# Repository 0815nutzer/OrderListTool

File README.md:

# OrderListTool
Create an order list from a BOM

Documentation: https://github.com/0815nutzer/OrderListTool/wiki

Dependencies: python3-pyqt5

English description see below.

## German description
Mit Hilfe dieses kleinen Werkzeugs soll eine automatisierte Zuordnung von Bestellnummern zu Bauteilen in einem Schaltplan erfolgen.
Die Bauteile des Schaltplan müssen hierfür in einer entsprechend formatierten csv-Datei zur Verfügung stehen, während die "Bauteildatenbank", welche die zuzuordnenden Bestellnummern enthält, aus entsprechend formatierten Textdateien besteht.

Eine ausführlichere Dokumentation befindet sich im Wiki dieses Projekts: https://github.com/0815nutzer/OrderListTool/wiki

### Anwendung
1. Erzeugen einer Stückliste im csv-Format unter Verwendung des dem CAD-System entsprechenden Skripts im Ordner "BOM-Scripts"
2. Das Programm durch Ausführen der `main.py` mit Python3 starten
3. Mit Klick auf "Stückliste" die zuvor erstellte Stückliste im csv-Fomat wählen
4. Durch Klick auf "Bestelllisten" den Ordner mit den Bestelllisten wählen
5. Paare durch klicken auf "Suche Paare" suchen lassen
6. Die gefundenen Paare prüfen und wenn nötig, Änderungen in der Auswahl vornehmen
7. Mit Klick auf "exp. Bestellliste" die lieferantenspezifischen Bestelllisten generieren lassen

## English description

### Usage
1. Open schematic and create a BOM-file in csv-format using the appropriate script in the "BOM-Scripts"-folder
2. Start the tool by running `main.py` using python3
3. Select the prior created csv-file
4. Select the path to the folder containing the partlist-files
5. Click `Search pairs`
6. Review found matches and adjust, if required
7. Click `Export lists` to create distribtor dependend order lists

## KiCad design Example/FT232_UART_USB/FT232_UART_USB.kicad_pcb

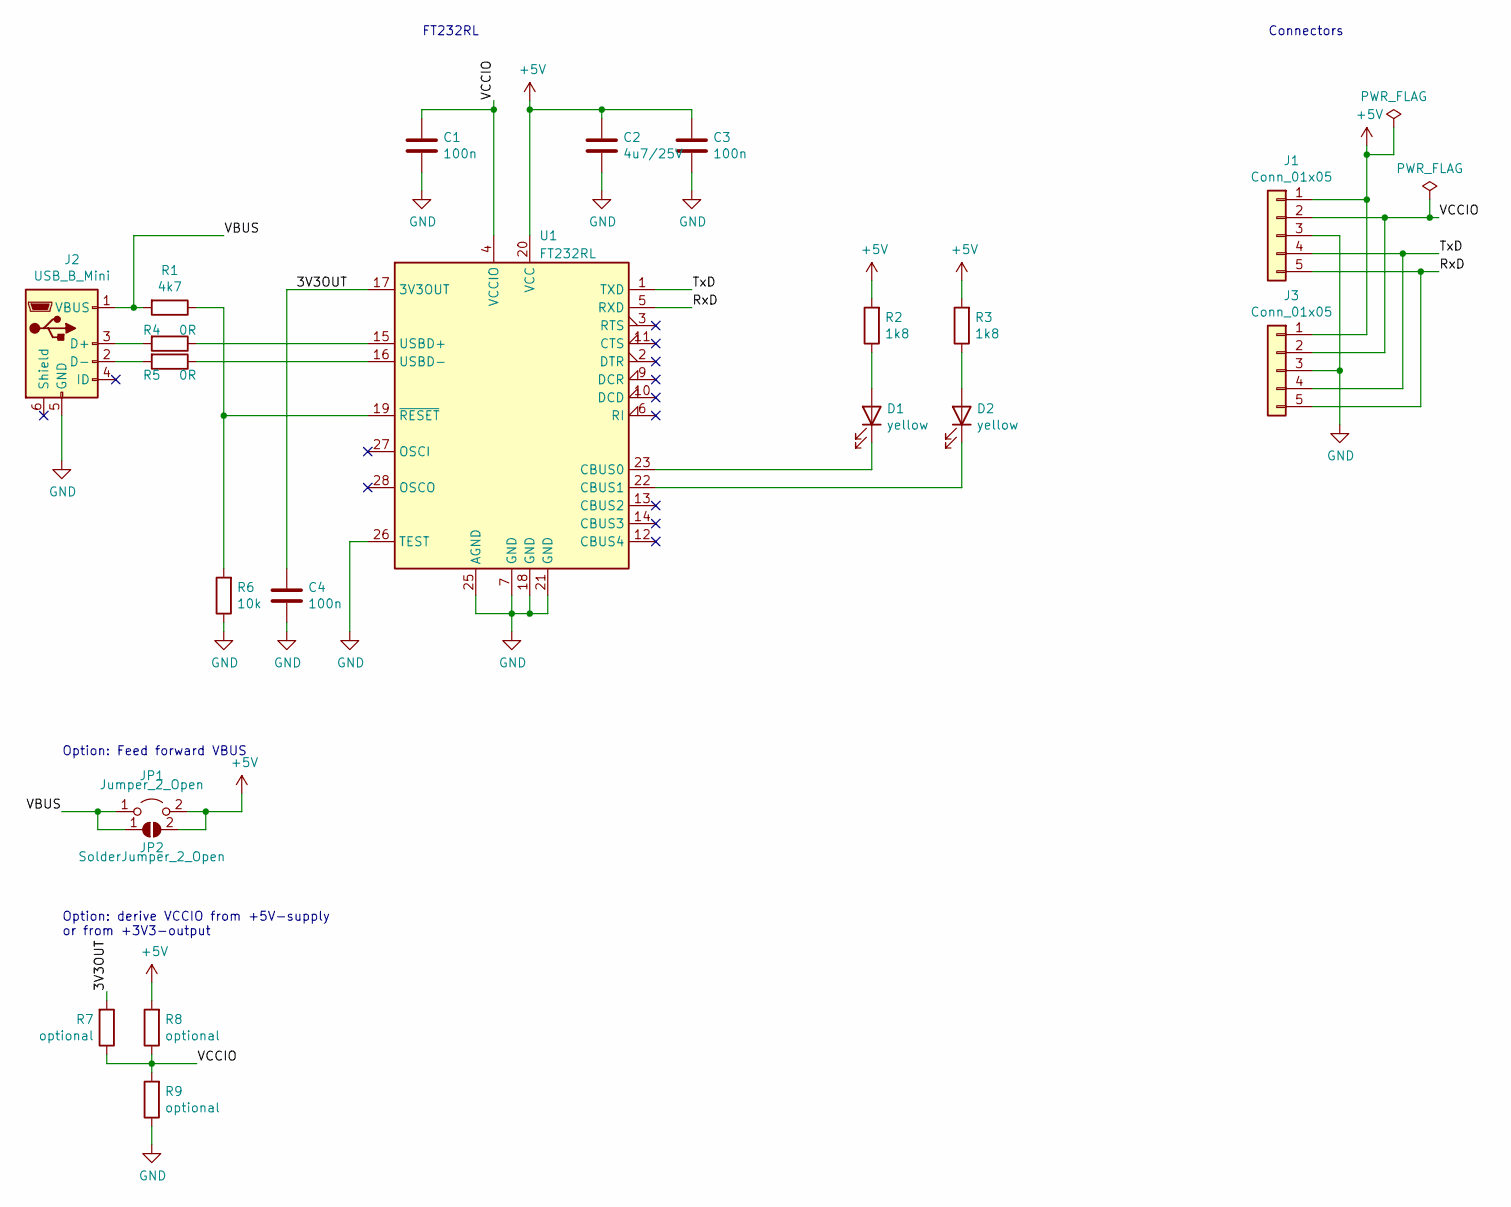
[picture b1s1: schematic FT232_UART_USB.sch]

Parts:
C1, C3, C4: 100n; C_0603_1608Metric
C2: 4u7/25V; C_1206_3216Metric
D1, D2: yellow; LED_0603_1608Metric
J1, J3: Conn_01x05; PinHeader_1x05_P2.54mm_Vertical
J2: USB_B_Mini; USB_Mini-B_Wuerth_65100516121_Horizontal
JP1: Jumper_2_Open; PinHeader_1x02_P2.54mm_Vertical
JP2: SolderJumper_2_Open; SolderJumper-2_P1.3mm_Open_TrianglePad1.0x1.5mm
R1: 4k7; R_0603_1608Metric
R2, R3: 1k8; R_0603_1608Metric
R4, R5: 0R; R_0603_1608Metric
R6: 10k; R_0603_1608Metric
R7, R8, R9: optional; R_0603_1608Metric
U1: FT232RL; SSOP-28_5.3x10.2mm_P0.65mm

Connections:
+5V: C2.1, C3.1, J1.1, J3.1, JP1.2 (B), JP2.2 (B), R2.2, R3.2, R8.2, U1.20 (VCC)
/3V3OUT: C4.1, R7.2, U1.17 (3V3OUT)
/RxD: J1.5, J3.5, U1.5 (RXD)
/TxD: J1.4, J3.4, U1.1 (TXD)
/VBUS: J2.1 (VBUS), JP1.1 (A), JP2.1 (A), R1.2
/VCCIO: C1.1, J1.2, J3.2, R7.1, R8.1, R9.2, U1.4 (VCCIO)
GND: C1.2, C2.2, C3.2, C4.2, J1.3, J2.5 (GND), J3.3, R6.1, R9.1, U1.7 (GND), U1.18 (GND), U1.21 (GND), U1.25 (AGND), U1.26 (TEST)
unnamed: D1.1 (K), U1.23 (CBUS0)
unnamed: D1.2 (A), R2.1
unnamed: D2.1 (K), U1.22 (CBUS1)
unnamed: D2.2 (A), R3.1
unnamed: J2.2 (D-), R5.2
unnamed: J2.3 (D+), R4.2
unnamed: R1.1, R6.2, U1.19 (~RESET~)
unnamed: R4.1, U1.15 (USBD+)
unnamed: R5.1, U1.16 (USBD-)

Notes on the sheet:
FT232RL
Connectors
Option: Feed forward VBUS
Option: derive VCCIO from +5V-supply or from +3V3-output

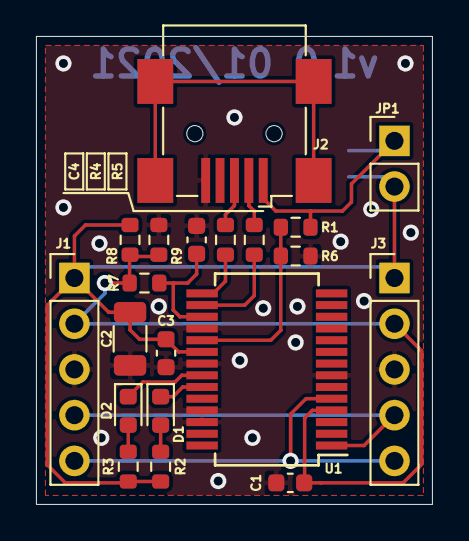
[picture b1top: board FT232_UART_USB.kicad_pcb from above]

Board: 2 copper layers, 22.0 x 26.0 mm, 21 parts (1 on the bottom side), 16 nets.

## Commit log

2021-03-25 initialer Stand des Programms hinzugefügt, Weiterentwicklung des Programms nun als eigenständiges Git-Projekt
2021-03-25 Dokumentation durch Anpassung der Readme-Datei begonnen.
2021-03-26 Mehrsprachigkeit implementiert. language.py beinhaltet die Texte der jeweiligen Sprache (aktuell Deutsch und Englisch) und kann beliebig für jede Sprache erweitert werden. Auswahl der Sprach erfolgt 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
2021-03-26 fehlende Sprachdatei nachgeliefert, kleiner Anpassung bezüglich der Definitionen
2021-03-30 Für Bestelllisten zu ignorierende Bauteile werden bei der Gesamtübersicht nicht mehr ignoriert, diverse Anpassungen im Zusammenhang mit der Dokumentation
2021-03-30 Lizenzinformationen hinzugefügt (GPLv3)
2021-03-30 Lizenz auf oberste Ebene verschoben
2021-04-03 Den USB_UART_Adapter als KiCAD-Projekt in Beispiele eingefügt, um auch die BOM-Skripte erproben zu können
2021-04-03 Verweis auf Wiki zu README hinzugefügt.
2021-04-19 Stücklisten um Eigenschaft "Herstellerbezeichnung" (Manufacturer -> MANNUM) erweitert, damit Bestücklisten für Hersteller erzeugt werden können, da diese die Herstellernummer anstelle der Bestellnumm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
2021-04-19 Eigenschaft "manNum" (Herstellerbezeichnung) hinzugefügt, um Bestückungslisten für Platinenfertiger zu generieren
2021-06-30 Symbol K (Relais) zu Teiletyp "mechanics" hinzugefügt
2021-08-13 Abhängigkeit von pyQt5 in ReadMe eingetragen
2021-08-27 Bauteileizelübersicht um Bauteilwert erweitert
